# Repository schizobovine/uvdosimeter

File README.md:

# UV Dosimeter

Microcontroller project to (somehow) get data from the SiLabs SI1145 UV index
sensor to a user such that they know when the daystar is out to kill them
(slowly, with cancer).

Various designs in the works, but the primary focus right now is a Bluetooth
4.0+ LE based sensor which communicates to a smart phone or watch for data
logging and handling any user interaction/warnings. This cuts out the need for
a display, controls (beyond a power switch), and notification system.

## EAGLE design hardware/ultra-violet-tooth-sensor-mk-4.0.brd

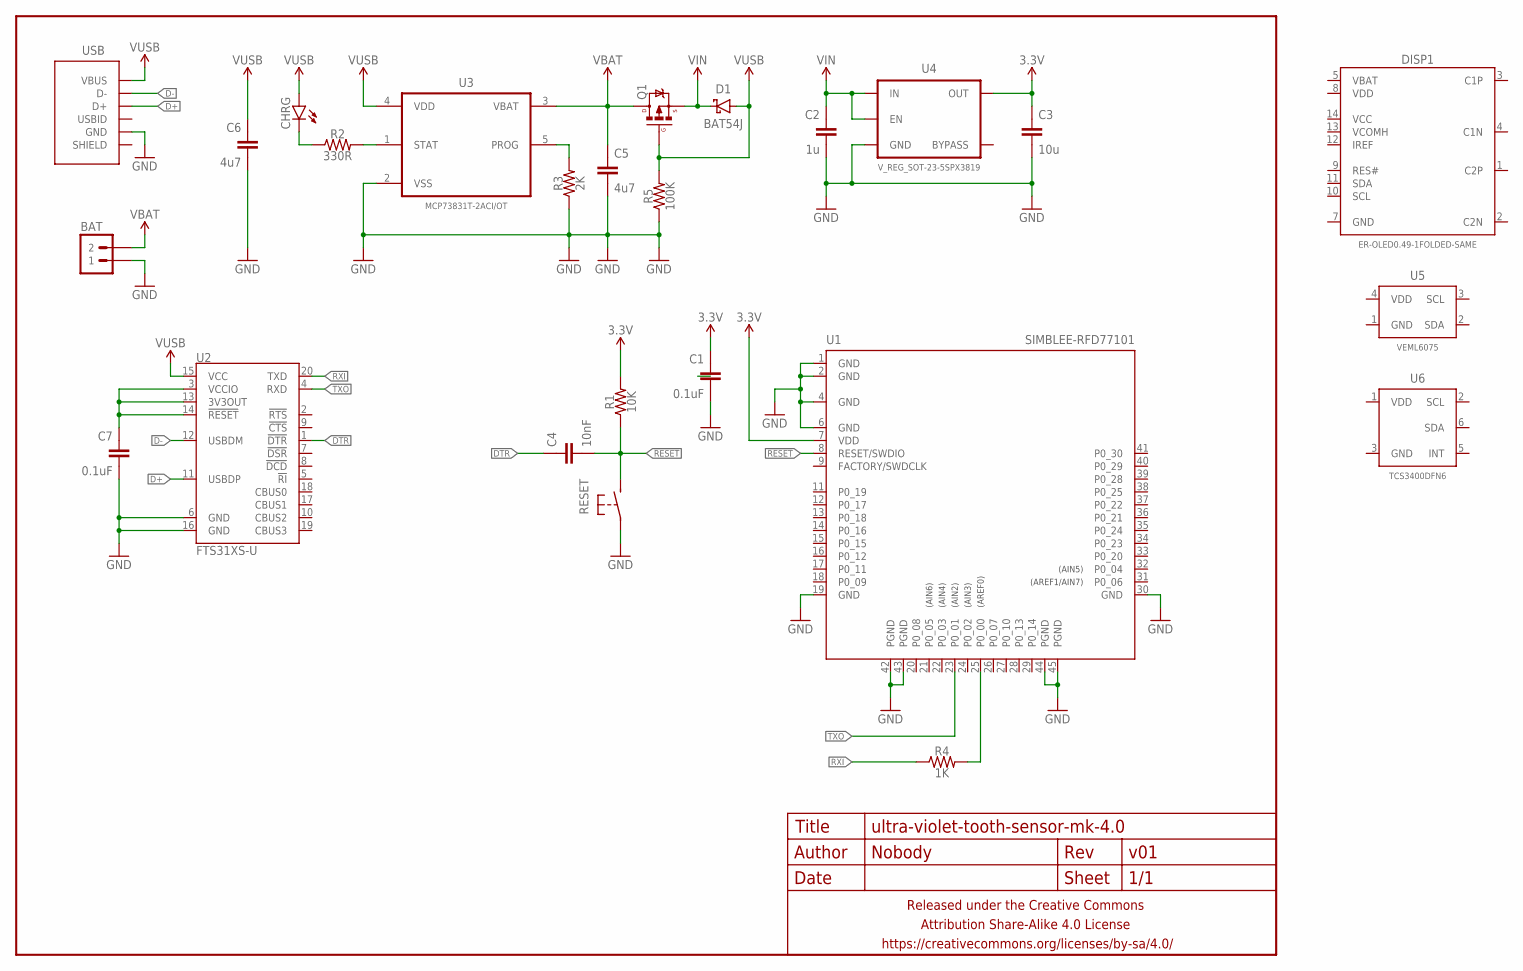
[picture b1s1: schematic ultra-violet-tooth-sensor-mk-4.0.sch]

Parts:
BAT: M02JST-2MM-SMT; JST-2-SMD
C1, C7: 0.1uF; C0402
C2: 1u; C0603-TIGHTER
C3: 10u; C0603-TIGHTER
C4: 10nF; C0402
C5, C6: 4u7; C0603-TIGHTER
CHRG: LED0603-TIGHT; LED-0603-TIGHT
D1: BAT54J; SOD323-SCHOTTKY
DISP1: ER-OLED0.49-1FOLDED-SAME; ER-OLED0.49-1-FOLDED-SAME
FRAME1: FRAME-LETTERNO_PACKAGE; DUMMY
Q1: MOSFET-PCHANNELSOT-23; SOT23
R1: 10K; R0402
R2: 330R; R0402
R3: 2K; R0402
R4: 1K; R0402
R5: 100K; R0402
RESET: SPST-NO-TACTSMD-TINIER; TACTILE_SWITCH_SMD_TINY
U1: SIMBLEE-RFD77101; RFD77101
U2: FTS31XS-U; SSOP20_L
U3: MCP73831T-2ACI/OT; SOT95P280X145-5N
U4: V_REG_SOT-23-5SPX3819; SOT23-5
U5: VEML6075; OPLGA4
U6: TCS3400DFN6; TCS3400_DFN6
USB: USB-AB-SHIELDFCI-10118193-USB-MICRO-B; FCI-10118193-USB-MICRO-B

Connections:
3.3V: C1.1, C3.1, R1.2, U1.7 (VDD), U4.5 (OUT)
!RESET: C4.2, R1.1, RESET.P$2 (2), U1.8 (RESET/SWDIO)
D+: U2.11 (USBDP), USB.3 (D+)
D-: U2.12 (USBDM), USB.2 (D-)
DTR: C4.1, U2.1 (!DTR)
GND: BAT.2 (1), C1.2, C2.2, C3.2, C5.2, C6.2, C7.2, R3.1, R5.1, RESET.P$1 (1), U1.1 (GND), U1.2 (GND), U1.4 (GND), U1.6 (GND), U1.19 (GND), U1.30 (GND), U1.42 (PGND), U1.43 (PGND), U1.44 (PGND), U1.45 (PGND), U2.6 (GND), U2.16 (GND), U3.2 (VSS), U4.2 (GND), USB.5 (GND)
unnamed: CHRG.C, R2.1
unnamed: R4.2, U1.25 (P0_00)
unnamed: C7.1, U2.3 (VCCIO), U2.13 (3V3OUT), U2.14 (!RESET)
unnamed: R3.2, U3.5 (PROG)
unnamed: R2.2, U3.1 (STAT)
RXI: R4.1, U2.20 (TXD)
TXO: U1.23 (P0_01), U2.4 (RXD)
VBAT: BAT.1 (2), C5.1, Q1.3 (D), U3.3 (VBAT)
VIN: C2.1, D1.C, Q1.2 (S), U4.1 (IN), U4.3 (EN)
VUSB: C6.1, CHRG.A, D1.A, Q1.1 (G), R5.2, U2.15 (VCC), U3.4 (VDD), USB.1 (VBUS)

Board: 2 copper layers, 26 parts (1 on the bottom side), 16 nets, no tracks yet.

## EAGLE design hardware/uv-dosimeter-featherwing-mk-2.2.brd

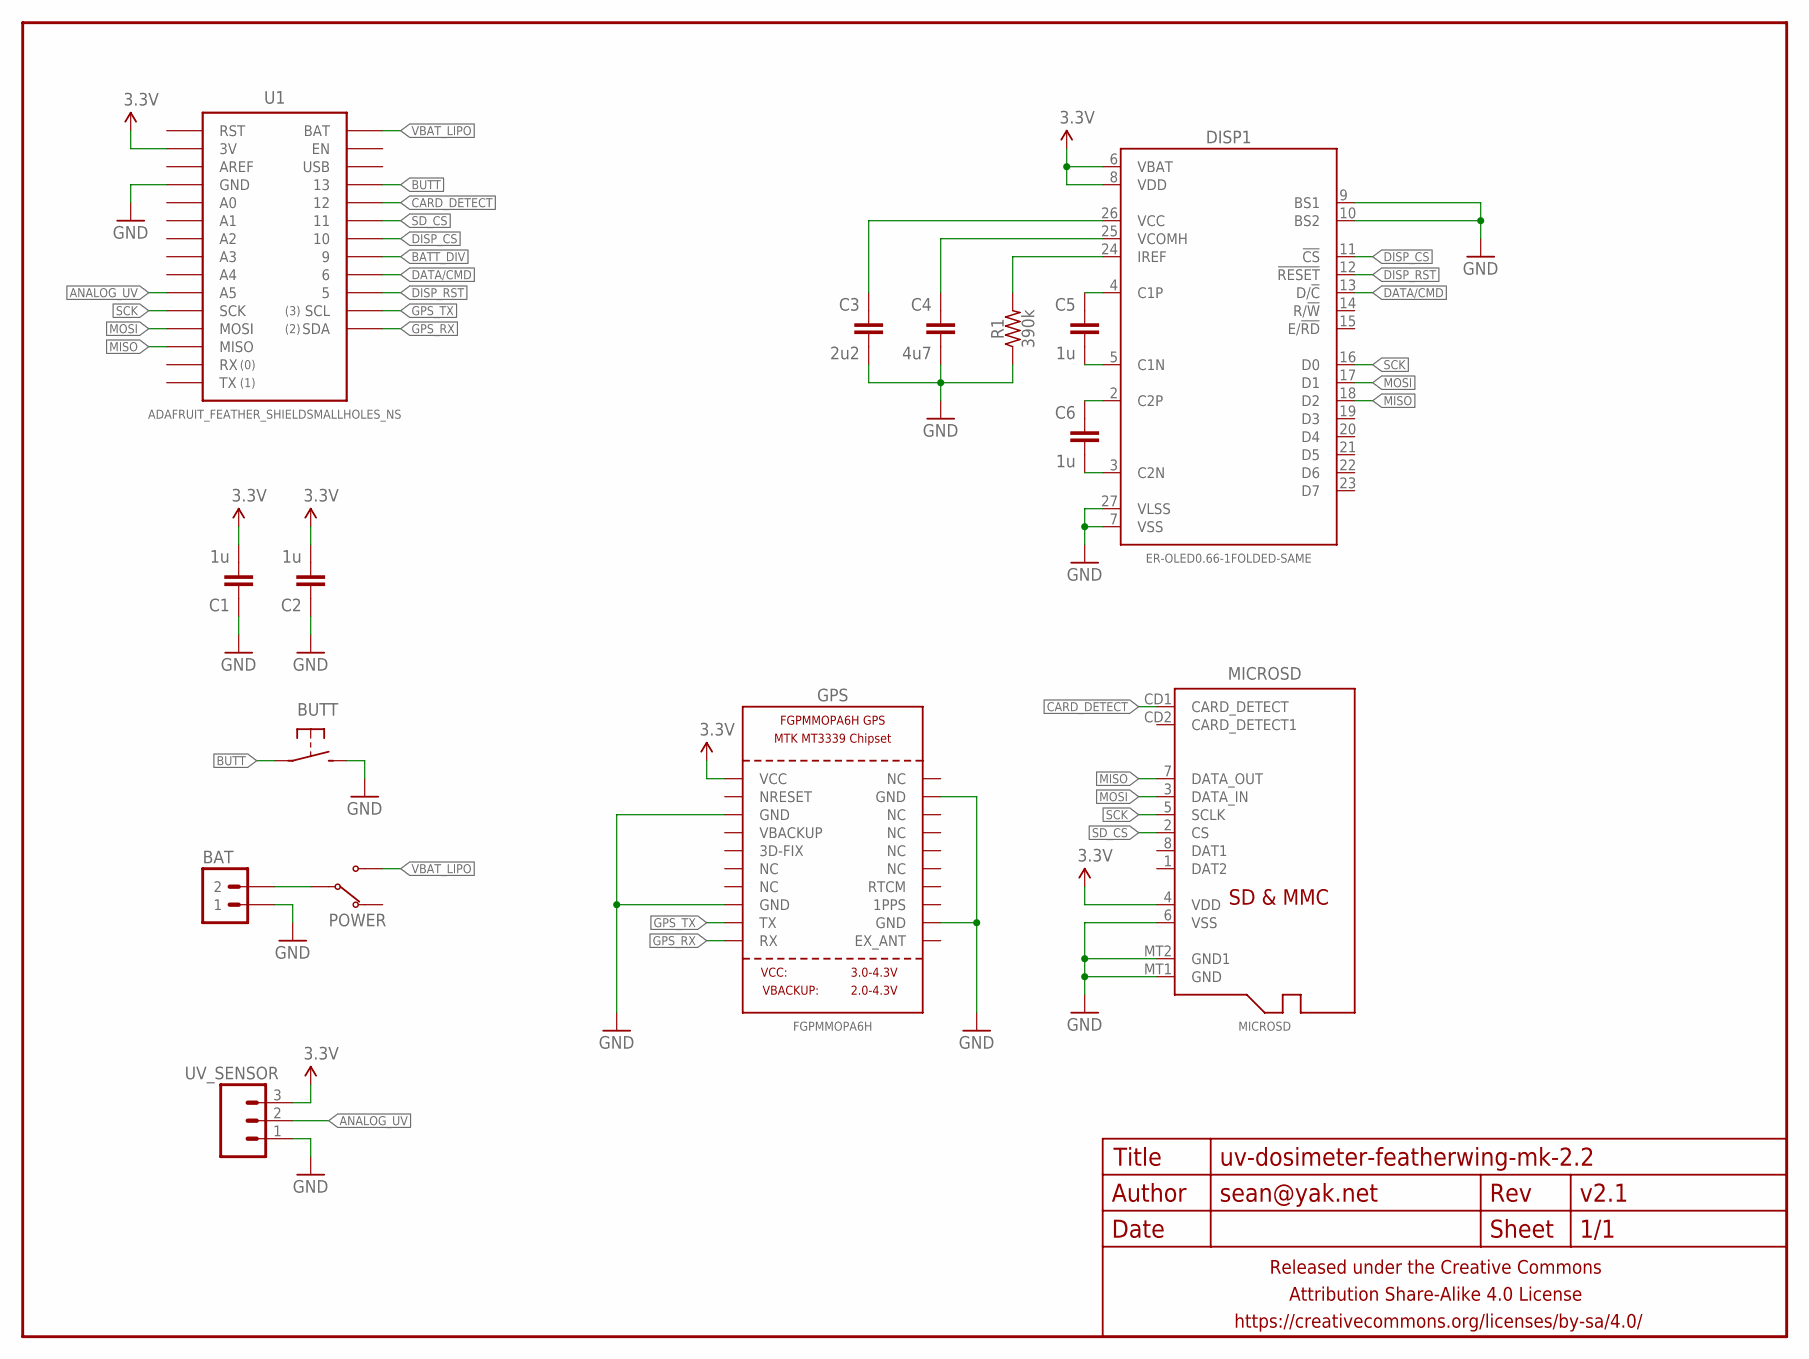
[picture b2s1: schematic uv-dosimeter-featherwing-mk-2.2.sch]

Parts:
BAT: M02JST-2MM-SMT; JST-2-SMD
BUTT: SPST-NO-TACT3MM-PTH-SMALL-PADS; DTS-3-SMALL-PADS
C1, C2, C5, C6: 1u; C0603
C3: 2u2; C0603
C4: 4u7; C0603
DISP1: ER-OLED0.66-1FOLDED-SAME; ER-OLED0.66-1-FOLDED-SAME
FRAME1: FRAME-LETTERNO_PACKAGE; DUMMY
GPS: FGPMMOPA6H
MICROSD: MICROSD
POWER: SWITCH-SPDTPTH-VERT-2.54MM; SWITCH-SPDT
R1: 390k; R0603
U1: ADAFRUIT_FEATHER_SHIELDSMALLHOLES_NS; ADAFRUIT_FEATHER_SMALLHOLES_NS
UV_SENSOR: M03PTH-CENTERED; 1X03-CENTERED

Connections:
3.3V: C1.2, C2.2, DISP1.6 (VBAT), DISP1.8 (VDD), GPS.P$1 (VCC), MICROSD.4 (VDD), U1.3V, UV_SENSOR.3
ANALOG_UV: U1.A5, UV_SENSOR.2
BATT_DIV: U1.9
BUTT: BUTT.1, U1.13
CARD_DETECT: MICROSD.CD1 (CARD_DETECT), U1.12
DATA/CMD: DISP1.13 (D/!C), U1.6
DISP_CS: DISP1.11 (!CS), U1.10
DISP_RST: DISP1.12 (!RESET), U1.5
GND: BAT.2 (1), BUTT.2, C1.1, C2.1, C3.2, C4.2, DISP1.7 (VSS), DISP1.9 (BS1), DISP1.10 (BS2), DISP1.27 (VLSS), GPS.P$3 (GND), GPS.P$8 (GND), GPS.P$12 (GND), GPS.P$19 (GND), MICROSD.6 (VSS), MICROSD.MT1 (GND), MICROSD.MT2 (GND1), R1.1, U1.GND@0 (GND), U1.GND@1 (GND), UV_SENSOR.1
GPS_RX: GPS.P$10 (RX), U1.SDA
GPS_TX: GPS.P$9 (TX), U1.SCL
MISO: DISP1.18 (D2), MICROSD.7 (DATA_OUT), U1.MISO
MOSI: DISP1.17 (D1), MICROSD.3 (DATA_IN), U1.MOSI
unnamed: C5.1, DISP1.4 (C1P)
unnamed: BAT.1 (2), POWER.2 (COM)
unnamed: C5.2, DISP1.5 (C1N)
unnamed: C6.1, DISP1.2 (C2P)
unnamed: C6.2, DISP1.3 (C2N)
unnamed: DISP1.24 (IREF), R1.2
unnamed: C4.1, DISP1.25 (VCOMH)
unnamed: C3.1, DISP1.26 (VCC)
SCK: DISP1.16 (D0), MICROSD.5 (SCLK), U1.SCK
SD_CS: MICROSD.2 (CS), U1.11
VBAT_LIPO: POWER.3 (NO), U1.BAT

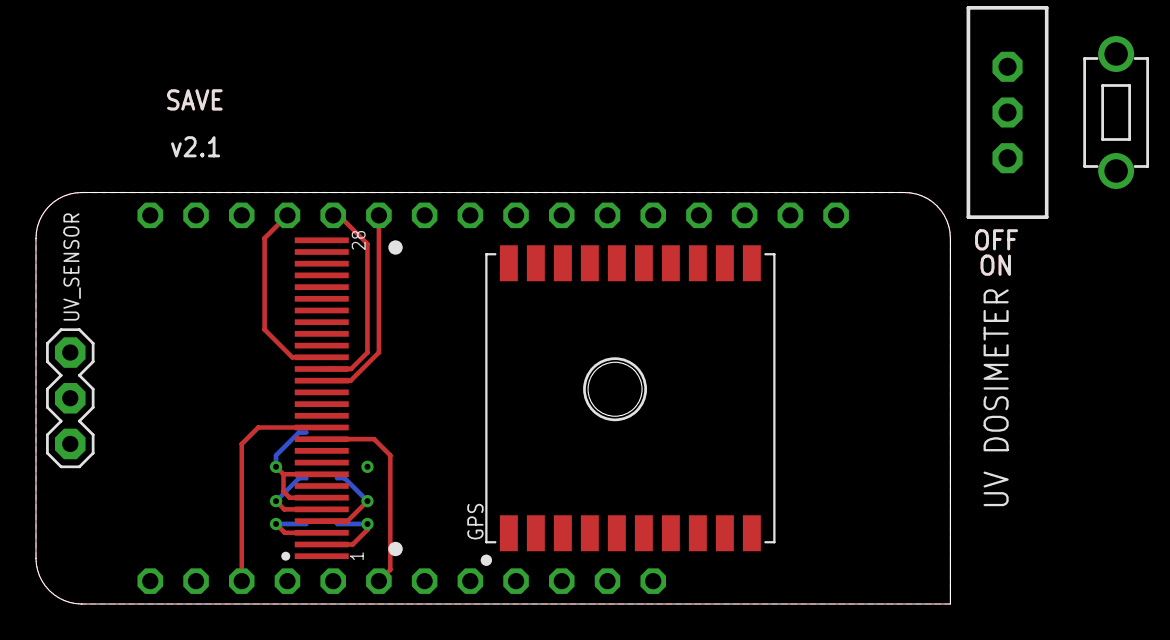
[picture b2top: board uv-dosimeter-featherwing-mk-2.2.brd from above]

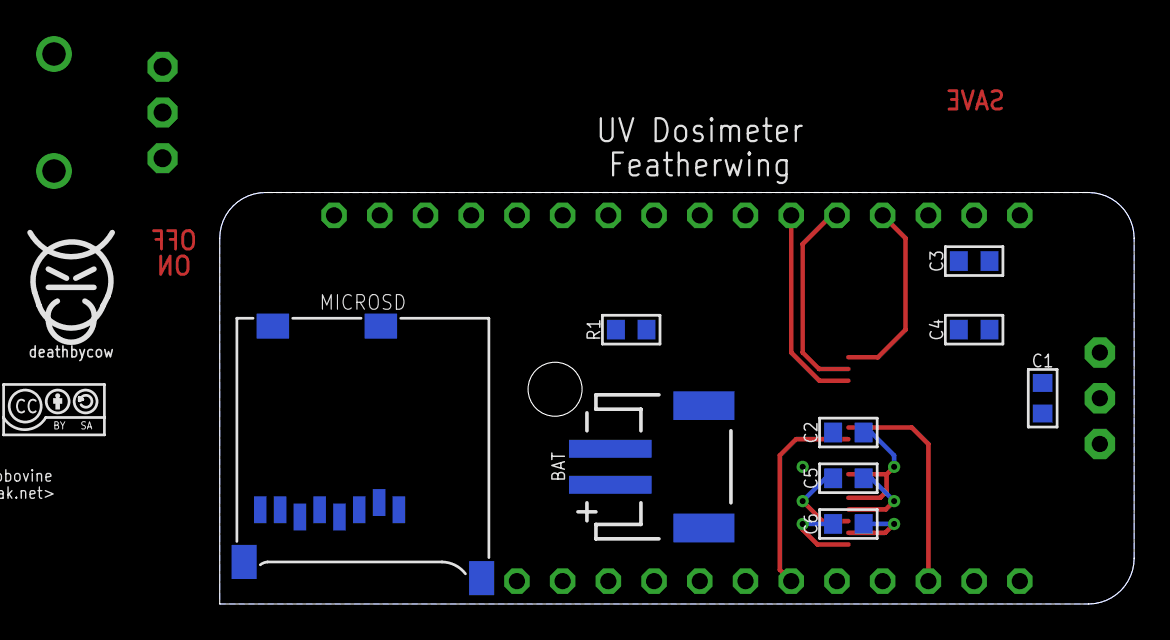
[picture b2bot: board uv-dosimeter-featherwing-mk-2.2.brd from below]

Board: 2 copper layers, 50.8 x 22.9 mm, 18 parts (12 on the bottom side), 23 nets.

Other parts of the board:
U$1: COW_SMALL
U$5: CC-BY-SA-4.0-NO-URL

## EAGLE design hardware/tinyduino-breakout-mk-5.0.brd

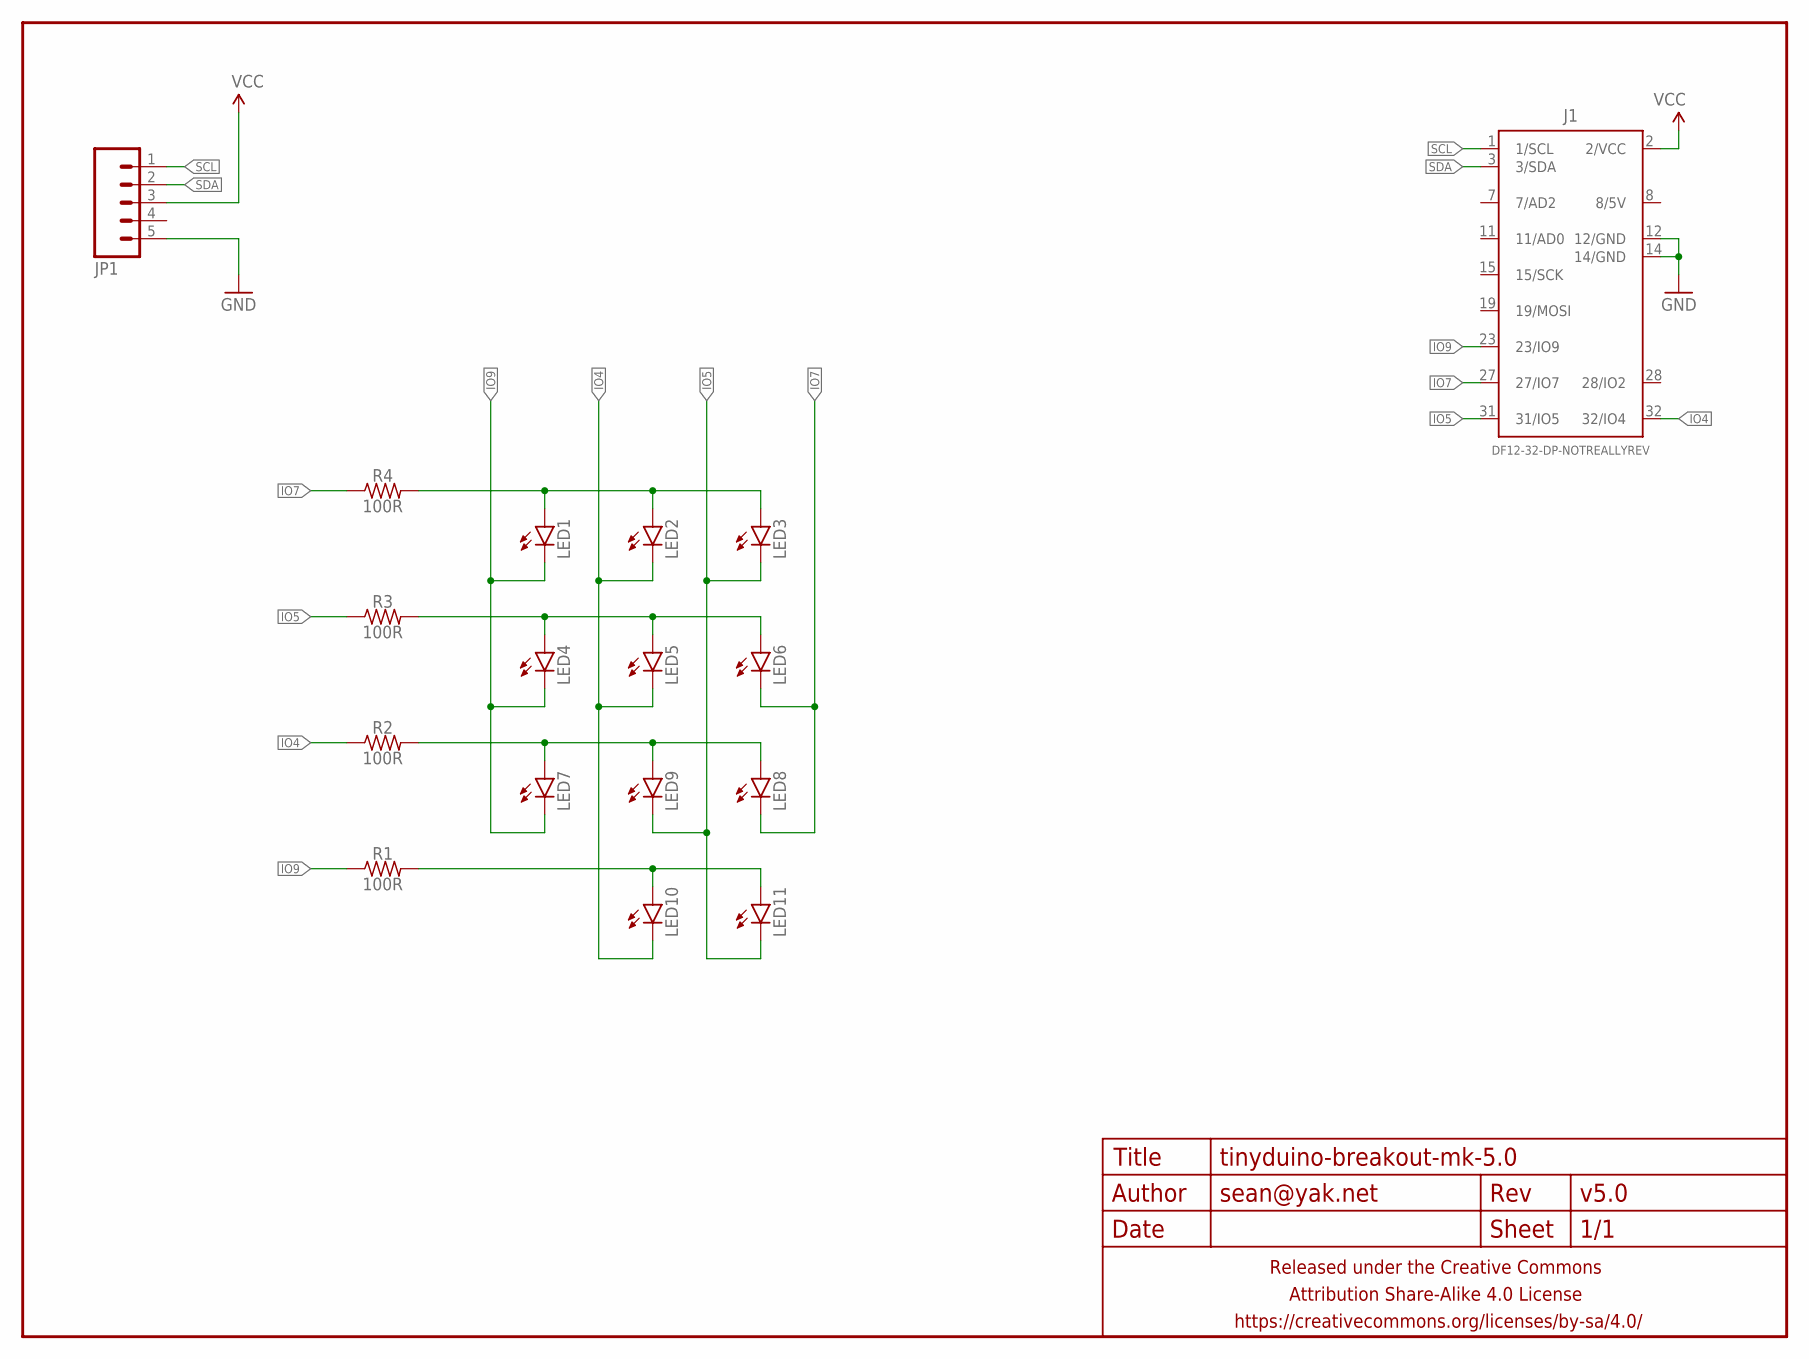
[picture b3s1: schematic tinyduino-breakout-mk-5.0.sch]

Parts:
FRAME1: FRAME-LETTERNO_PACKAGE; DUMMY
J1: DF12-32-DP-NOTREALLYREV; DF12-32-DP-I2C+EXTRA-REV
JP1: M05SMD-SHORT; 1X05-SMD-SHORT
LED1, LED2, LED3, LED4, LED5, LED6, LED7, LED8, LED9, LED10, LED11: LED0603; LED-0603
R1, R2, R3, R4: 100R; R0603

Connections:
GND: J1.12 (12/GND), J1.14 (14/GND), JP1.5
IO4: J1.32 (32/IO4), LED2.C, LED5.C, LED10.C, R2.1
IO5: J1.31 (31/IO5), LED3.C, LED9.C, LED11.C, R3.1
IO7: J1.27 (27/IO7), LED6.C, LED8.C, R4.1
IO9: J1.23 (23/IO9), LED1.C, LED4.C, LED7.C, R1.1
unnamed: LED1.A, LED2.A, LED3.A, R4.2
unnamed: LED4.A, LED5.A, LED6.A, R3.2
unnamed: LED7.A, LED8.A, LED9.A, R2.2
unnamed: LED10.A, LED11.A, R1.2
SCL: J1.1 (1/SCL), JP1.1
SDA: J1.3 (3/SDA), JP1.2
VCC: J1.2 (2/VCC), JP1.3

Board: 2 copper layers, 18 parts (4 on the bottom side), 12 nets, no tracks yet.

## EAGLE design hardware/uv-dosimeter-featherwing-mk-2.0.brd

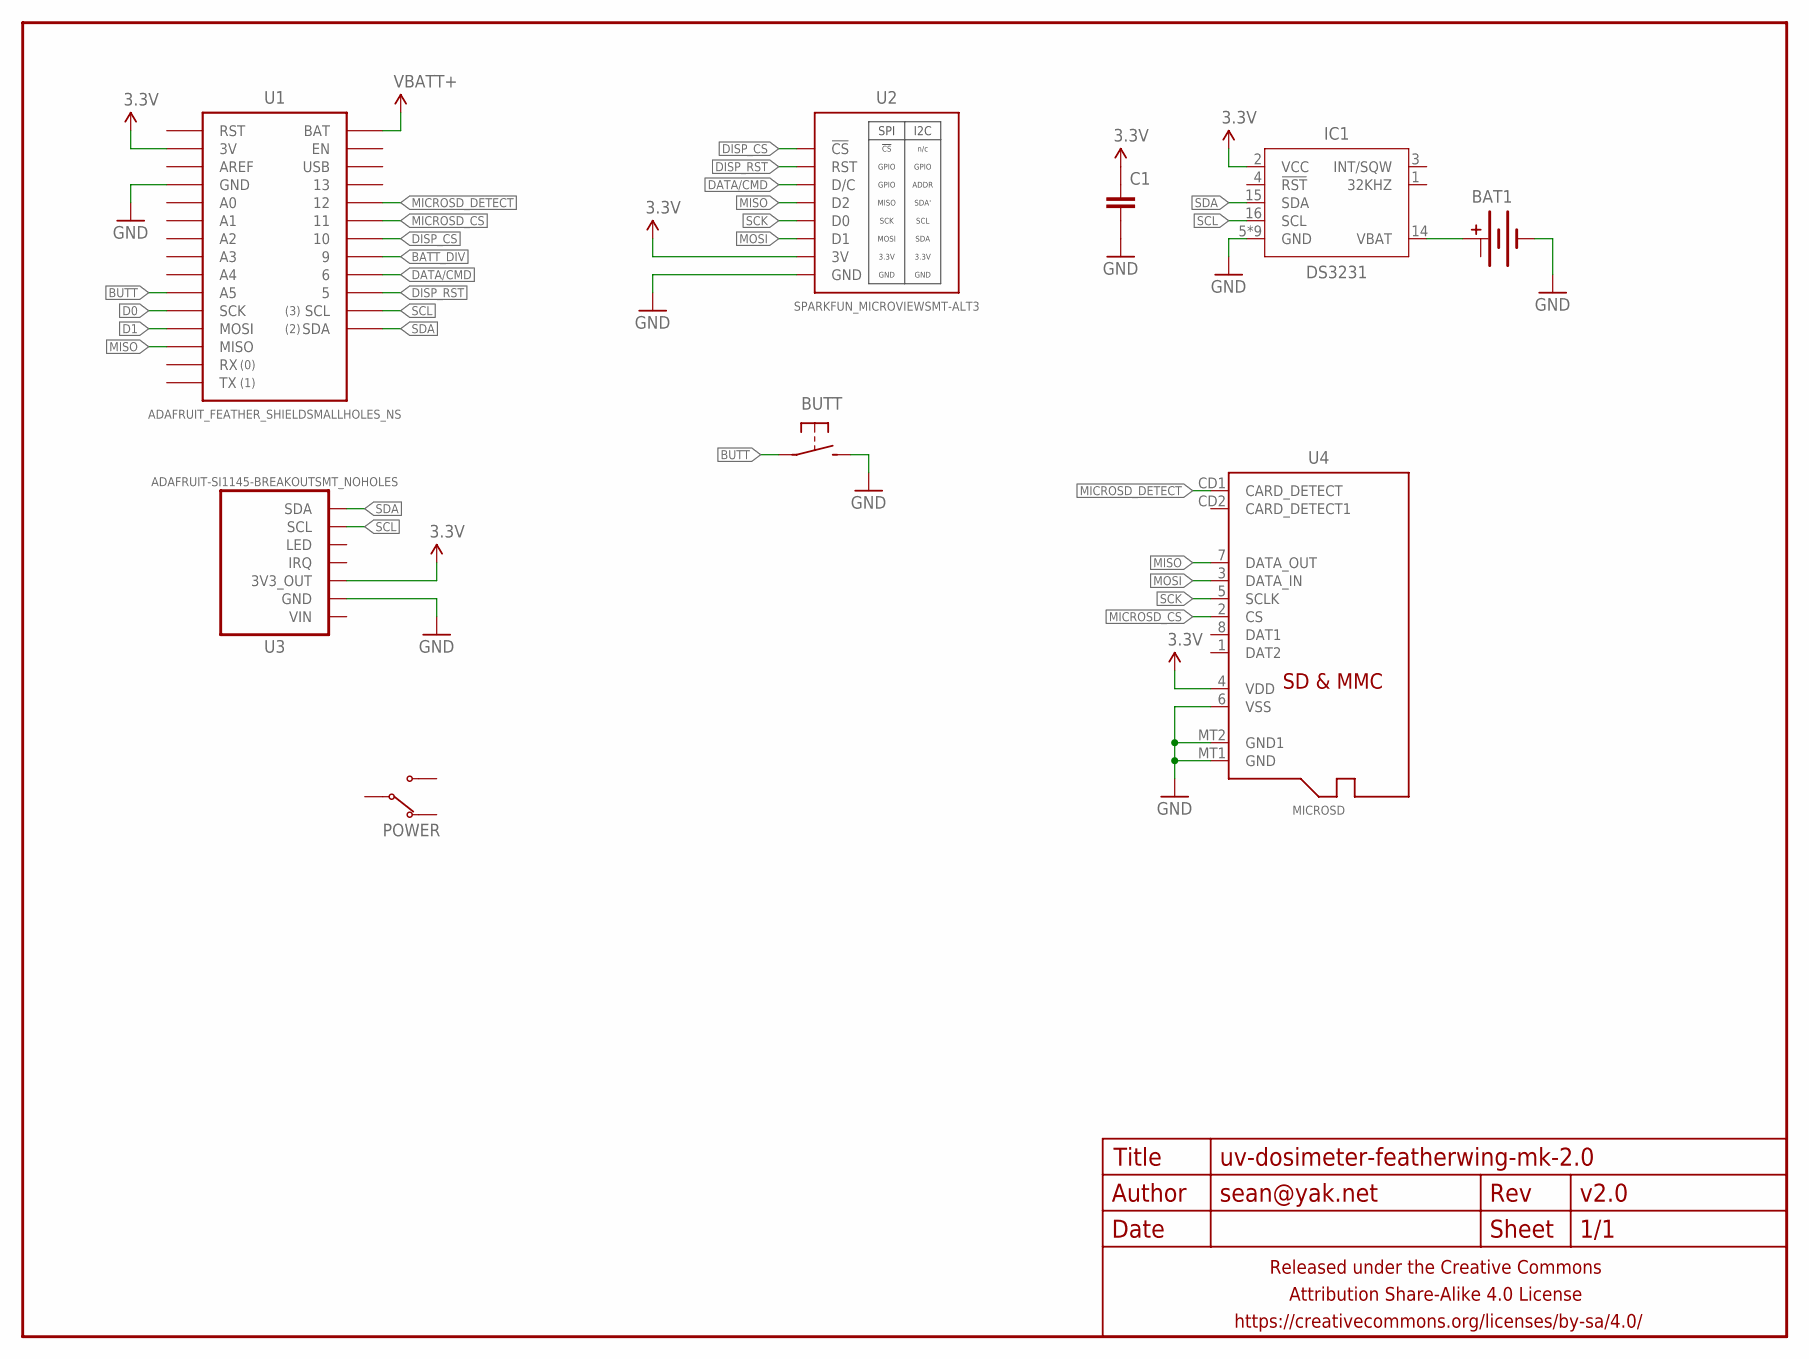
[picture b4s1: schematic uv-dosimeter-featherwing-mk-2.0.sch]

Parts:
BAT1: BATTERY-COINCR1225_SMD_SMALLER; BATTCON_12MM_SMD
BUTT: SPST-NO-TACT3MM-SMD; DTSM-3
C1: CAPACITOR-CERAMICC0603; C0603
FRAME1: FRAME-LETTERNO_PACKAGE; DUMMY
IC1: DS3231; SO16W
POWER: SWITCH-SPDTSMD-RA; SWITCH-SPDT-SMD-RA
U1: ADAFRUIT_FEATHER_SHIELDSMALLHOLES_NS; ADAFRUIT_FEATHER_SMALLHOLES_NS
U2: SPARKFUN_MICROVIEWSMT-ALT3; SPARKFUN-MICROVIEW-SMT-ALT3
U3: ADAFRUIT-SI1145-BREAKOUTSMT_NOHOLES; ADAFRUIT-SI1145-BREAKOUT-SMT-NOHOLES
U4: MICROSD

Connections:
3.3V: C1.1, IC1.2 (VCC), U1.3V, U2.3V, U3.3V3 (3V3_OUT)
BATT_DIV: U1.9
BUTT: BUTT.1, U1.A5
D0: U1.SCK
D1: U1.MOSI
DATA/CMD: U1.6, U2.D/C
DISP_CS: U1.10, U2.CS (!CS)
DISP_RST: U1.5, U2.RST
GND: BAT1.-, BUTT.2, C1.2, IC1.5 (GND), IC1.6 (GND), IC1.7 (GND), IC1.8 (GND), IC1.9 (GND), IC1.10 (GND), IC1.11 (GND), IC1.12 (GND), IC1.13 (GND), U1.GND@0 (GND), U1.GND@1 (GND), U2.GND, U3.GND, U4.6 (VSS), U4.MT1 (GND)
MICROSD_CS: U1.11, U4.2 (CS)
MICROSD_DETECT: U1.12, U4.CD1 (CARD_DETECT)
MISO: U1.MISO, U2.D2, U4.7 (DATA_OUT)
MOSI: U2.D1, U4.3 (DATA_IN)
unnamed: BAT1.+@1 (+), IC1.14 (VBAT)
SCK: U2.D0, U4.5 (SCLK)
SCL: IC1.16 (SCL), U1.SCL, U3.SCL
SDA: IC1.15 (SDA), U1.SDA, U3.SDA
VBATT+: U1.BAT
VDD: U4.4 (VDD)

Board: 2 copper layers, 12 parts (7 on the bottom side), 14 nets, no tracks yet.

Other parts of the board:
U$1: COW_SMALL
U$5: CC-BY-SA-4.0-NO-URL

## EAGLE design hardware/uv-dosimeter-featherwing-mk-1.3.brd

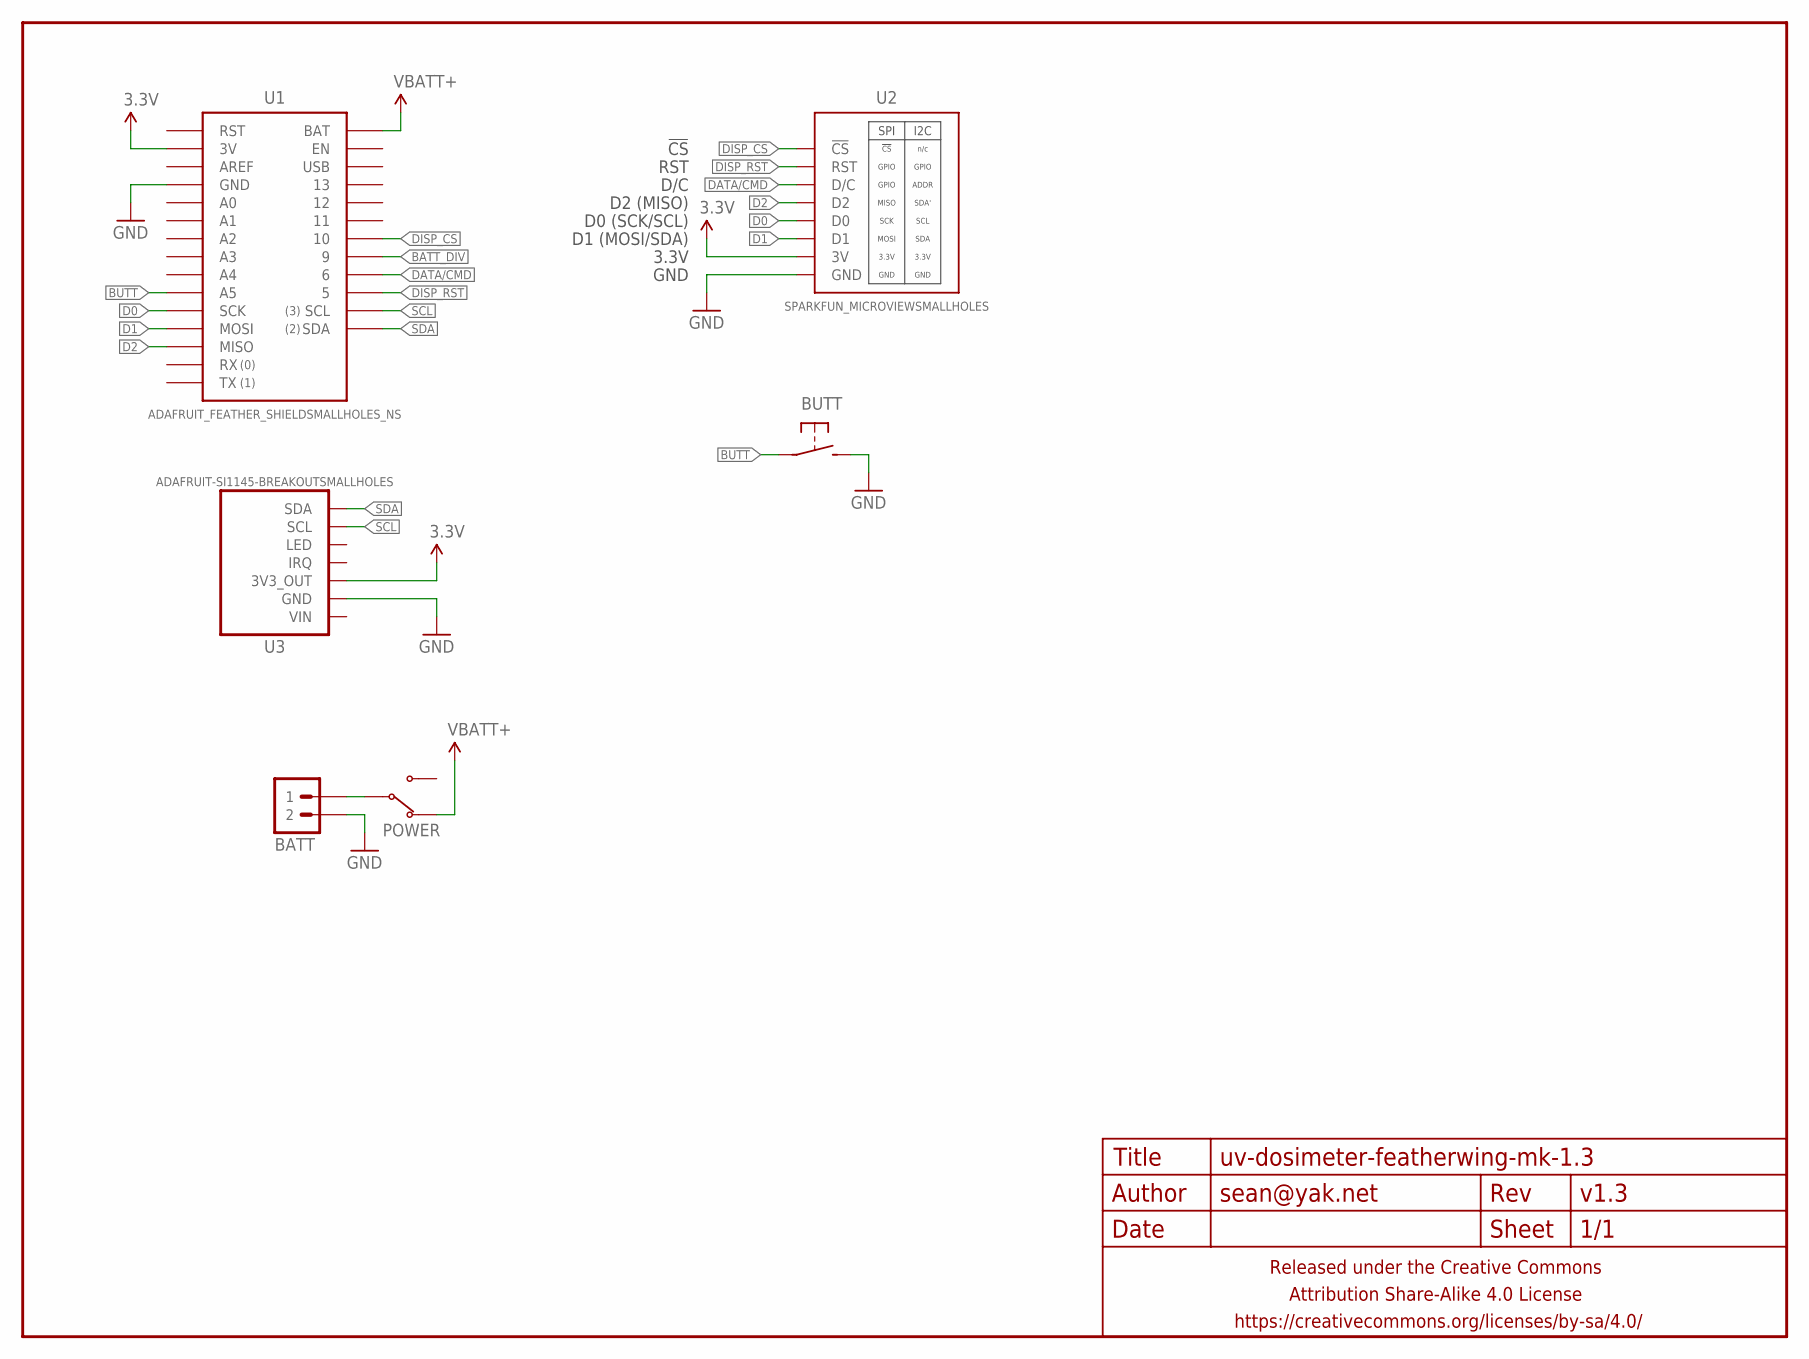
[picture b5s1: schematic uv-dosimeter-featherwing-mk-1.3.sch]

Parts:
BATT: M02JST-2MM-SMT; JST-2-SMD
BUTT: SPST-NO-TACT3MM-PTH-SMALL-PADS; DTS-3-SMALL-PADS
FRAME1: FRAME-LETTERNO_PACKAGE; DUMMY
POWER: SWITCH-SPDTPTH-VERT-2.54MM; SWITCH-SPDT
U1: ADAFRUIT_FEATHER_SHIELDSMALLHOLES_NS; ADAFRUIT_FEATHER_SMALLHOLES_NS
U2: SPARKFUN_MICROVIEWSMALLHOLES; SPARKFUN-MICROVIEW-SMALLHOLES
U3: ADAFRUIT-SI1145-BREAKOUTSMALLHOLES; ADAFRUIT-SI1145-BREAKOUT-LESSSILK-SMALLHOLES

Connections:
3.3V: U1.3V, U2.3V, U3.3V3_OUT
BATT_DIV: U1.9
BUTT: BUTT.1, U1.A5
D0: U1.SCK, U2.D0
D1: U1.MOSI, U2.D1
D2: U1.MISO, U2.D2
DATA/CMD: U1.6, U2.D/C
DISP_CS: U1.10, U2.CS (!CS)
DISP_RST: U1.5, U2.RST
GND: BATT.1 (2), BUTT.2, U1.GND@0 (GND), U1.GND@1 (GND), U2.GND, U3.GND
unnamed: BATT.2 (1), POWER.2 (COM)
SCL: U1.SCL, U3.SCL
SDA: U1.SDA, U3.SDA
VBATT+: POWER.1 (NC), U1.BAT

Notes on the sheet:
GND
3.3V
D1 (MOSI/SDA)
D0 (SCK/SCL)
D2 (MISO)
D/C
RST
!CS

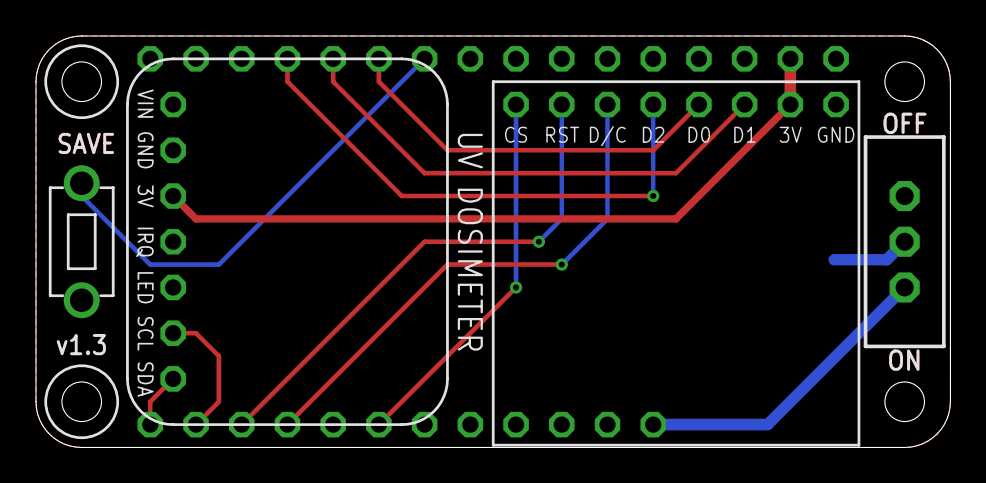
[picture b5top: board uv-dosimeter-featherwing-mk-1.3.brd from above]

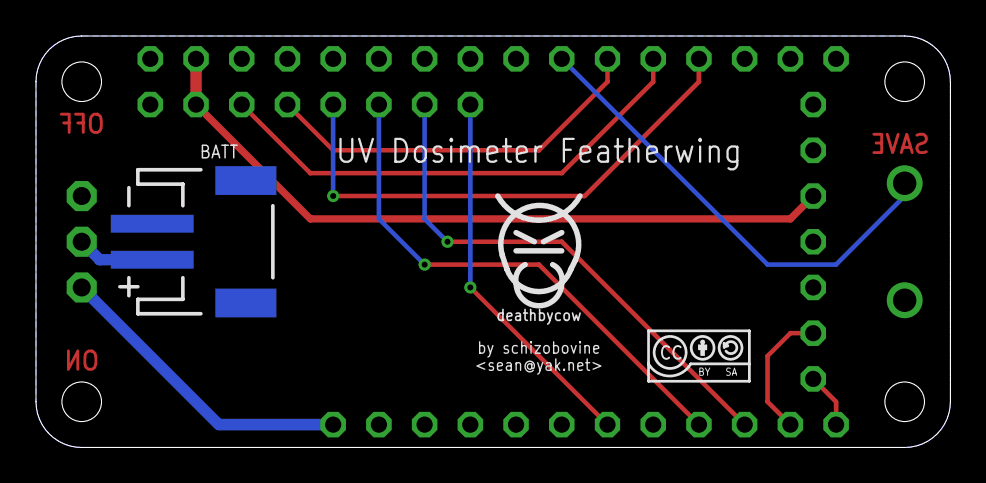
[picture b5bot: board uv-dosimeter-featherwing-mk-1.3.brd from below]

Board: 2 copper layers, 50.8 x 22.9 mm, 9 parts (4 on the bottom side), 13 nets.

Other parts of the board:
U$1: COW_SMALL
U$5: CC-BY-SA-4.0-NO-URL

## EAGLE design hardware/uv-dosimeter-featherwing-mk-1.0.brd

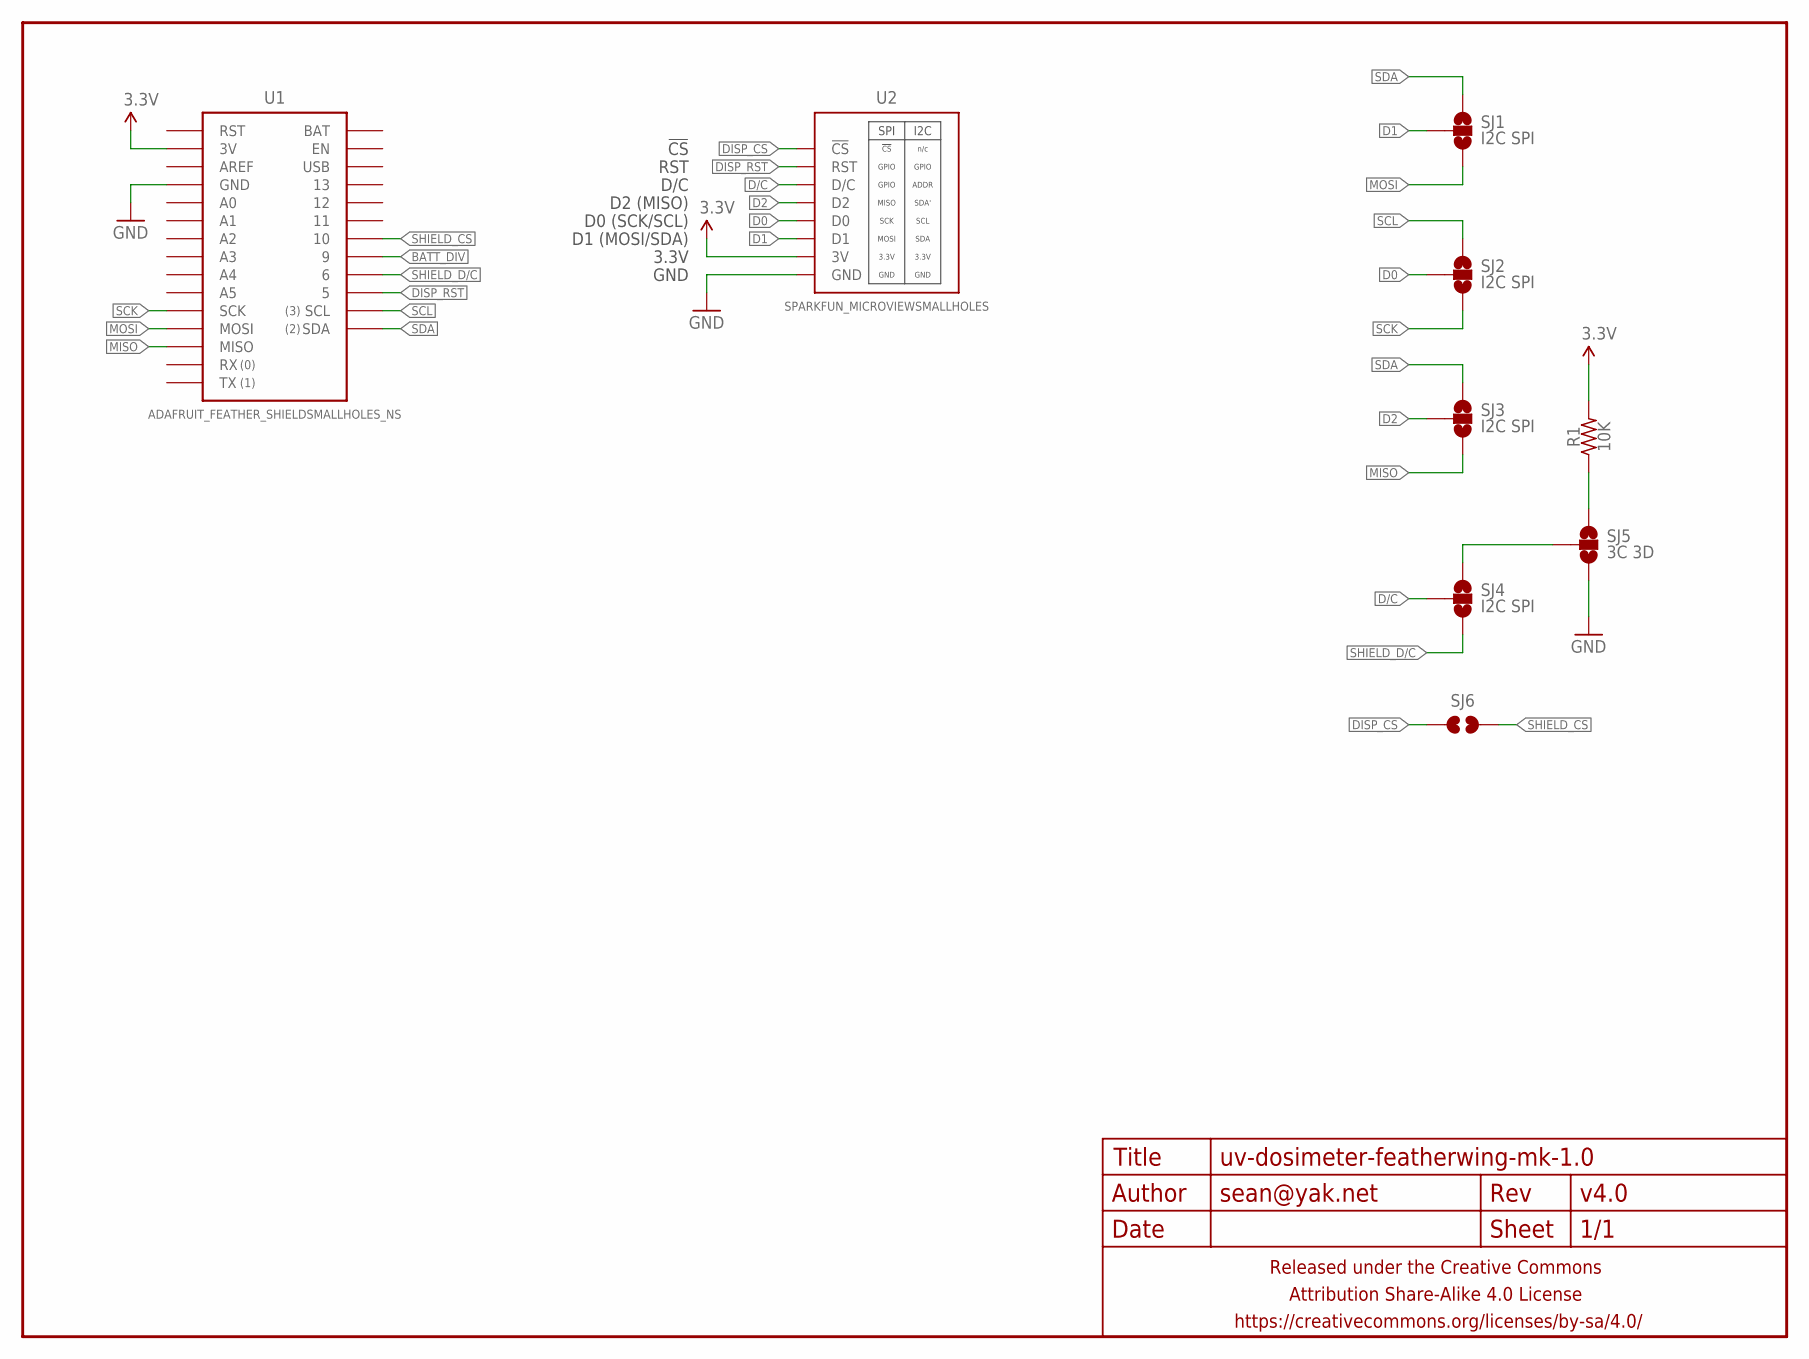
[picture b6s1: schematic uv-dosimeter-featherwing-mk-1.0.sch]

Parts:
FRAME1: FRAME-LETTERNO_PACKAGE; DUMMY
R1: 10K; R0603
SJ1, SJ2, SJ3, SJ4: I2C SPI; PAD-JUMPER-3-NO_YES_SILK_FULL_BOX
SJ5: 3C 3D; PAD-JUMPER-3-NO_YES_SILK_FULL_BOX
SJ6: JUMPER-PAD-2-NOYES_SILK; PAD-JUMPER-2-NO_YES_SILK
U1: ADAFRUIT_FEATHER_SHIELDSMALLHOLES_NS; ADAFRUIT_FEATHER_SMALLHOLES_NS
U2: SPARKFUN_MICROVIEWSMALLHOLES; SPARKFUN-MICROVIEW-SMALLHOLES

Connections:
3.3V: R1.2, U1.3V, U2.3V
BATT_DIV: U1.9
D0: SJ2.2, U2.D0
D1: U2.D1
D2: U2.D2
D/C: U2.D/C
DISP_CS: SJ6.1, U2.CS (!CS)
DISP_RST: U1.5, U2.RST
GND: SJ5.3, U1.GND@0 (GND), U1.GND@1 (GND), U2.GND
MISO: SJ3.3, U1.MISO
MOSI: SJ1.3, U1.MOSI
unnamed: R1.1, SJ5.1
unnamed: SJ4.1, SJ5.2
SCK: SJ2.3, U1.SCK
SCL: SJ2.1, U1.SCL
SDA: SJ1.1, U1.SDA
SHIELD_CS: SJ6.2, U1.10
SHIELD_D/C: SJ4.3, U1.6

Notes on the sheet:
GND
3.3V
D1 (MOSI/SDA)
D0 (SCK/SCL)
D2 (MISO)
D/C
RST
!CS

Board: 2 copper layers, 12 parts (3 on the bottom side), 14 nets, no tracks yet.

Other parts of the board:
U$1: COW_SMALL
U$3: OSHWLOGO_TINY_SILKONLY

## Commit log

2015-05-28 boards for first manufacture run
2015-05-29 new firmwares for the testses
2015-05-29 now with 50% more firmware!
2015-06-01 many new tries, but going with mk 3.2 for next batch to oshpark
2015-06-01 more dicking around
2015-06-22 more tweaking/twaddling
2015-07-05 quick and dirty demo version to show off
2015-07-06 ditching bluetooth support for now
2015-07-18 slightly less dirty version including rtc and microsd card for logging
2015-07-18 swap to adafruit SD library for bit-banging; python script to handle initial time-setting
2016-01-15 ohai
2016-01-15 switching to 128x32 version
2016-01-15 adding other submodules
2016-01-15 initial spec out
2016-01-15 More modules for the modularity?
2016-01-15 loosely working
2016-01-18 various attempts at a case for this thing
2016-01-18 power switchen
2016-01-18 adding revision number to file name
2016-01-18 adding revsion info to schematic and board
2016-01-18 new revision for new year
2016-01-18 tiny breakout attempt
2016-02-28 refinements to connector for tinyduino
2016-02-28 makefile
2016-02-28 si1145 lib
2016-02-28 more make making
2016-02-28 simple 0-11 display using charliplexed leds
2016-03-01 minor whitespace cleanup
2016-03-01 mark4, back to the full size breakout
2016-03-02 finished layout but unhappy w/choices
2016-03-02 i hate libraries sometimes
2016-03-02 relayout of charliplexed display only with 12 leds and connector for uv sensor (but nothing else
2016-04-16 featherwings to use sparkfun's microview plus adafruit's feather + uv sensor
2016-05-01 new layouts for featherwing
2016-05-01 first pass attempt at the opamp circuit for this UV photodiode
2016-05-01 drawings and autocad exports for laser-cut acrylic case
2016-05-01 change from symlinks that don't work across clients to submodules
2016-05-01 add sparkfun's oled lib
2016-05-01 initial code revision
2016-05-01 compiles now, stupid library differences
2016-05-01 jesus h christ this is a stupid limitation of the arduino gui
2016-05-01 to make the arduino gui less stupid
2016-05-01 graphics fixups
2016-05-01 more graphics fiddling
2016-05-03 removing these don't need 'em
2016-05-17 stupoduino compat
2016-05-17 new bards
2016-05-17 analog version for extra tinyness
2016-05-18 proper analog formula
2016-05-18 initial layout for UVA/B sensor board
2016-05-20 various relayouts of the opamp
2016-06-28 updating analog build script
2016-06-28 breakouts for the tinyduino version
2016-07-26 UV sensor testing firmware
2016-08-01 testing against other sensors
2016-08-01 simblee based uvdosimeter
2016-08-01 remove ml8511 b/c it wasn't working
2016-08-01 made BLE vs SD configurable
2016-08-02 more fiddling, need smaller usb to uart chip
2016-12-28 new board work

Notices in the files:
parts and their libraries:
A_butts: Released under the Creative Commons Attribution Share-Alike 4.0 License
A_butts: https://creativecommons.org/licenses/by-sa/4.0
A_butts: Released under the Creative Commons
